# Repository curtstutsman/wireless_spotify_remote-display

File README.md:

Wireless Spotify Remote Control and Display
Curt Stutsman & Nicholas Watanabe
https://github.com/curtstutsman/wireless_spotify_remote-display

Introduction
	Our group elected to implement a wireless Spotify remote control and album art display utilizing Spotify’s API to control the listening state of the user. Some features of the project include a rotary encoder (which doubled as a push button) and a 64x64 LED matrix. The rotary encoder was purposed for all input, allowing the user to adjust volume with rotations and toggle play/pause and skip to next or previous songs with single, double, and triple taps. The LED matrix was the primary output of the system, displaying in real time the album art of whatever song was currently playing. To achieve wireless communication with Spotify’s api, our group employed and ESP32-WROOM-32E wireless module. The rest of the functionality (LED driving, GPIO interface, etc.) was implemented on an STM32F103.

Figure 1: System Block Diagram

Hardware Overview
	Our project did not require an extensive list of hardware components to achieve the desired functionality. For the LED matrix, we used a 64x64 panel purchased from adafruit with a 2.5mm pitch. Each LED held a one bit value for each of red, green, and blue channels. The matrix as a whole was controlled via the HUB75 protocol, a standard for these types of LED matrices that utilized 16 different signals in the case of our matrix. The 16 signals of the HUB75 protocol were connected and controlled from the GPIO pins of the STM32. The rotary encoder was also controlled via GPIO pins on the MCU. We used a simple UART connection between the STM32 and the ESP32 to send commands to the ESP and to receive image data into the STM. A few other trivial components were included in the final PCB design such as reset buttons, headers for programming, and decoupling capacitors. The full schematic and PCB layout is given below and is linked on our github repository.

Figure 2: Schematic

Figure 3: PCB Layout

Software Overview
	Because we utilized two different chips in our project, the software was split between the STM32F103, which handled LED driving and input control, and the ESP32, which handled communication with the Spotify API and JPEG Decoding. All code can be found in the main.c file of the STM32 source code and the esp32_sketch.ino file of the ESP32 source code, both available on the github repo.

	The first functionality implemented was the button control. The rotary encoder consists of three signals, two for rotation encoding and one for the button. All three channels were connected to GPIO pins and configured to interrupt the CPU at the rising edge of the signal. Pushes to the button increase the tap count variable. The main loop would then check if tap count was greater than zero and enough time had passed since the last tap (to account for double and triple taps) and then send the corresponding command over UART to the ESP32. Interrupts for rotation of the encoder worked in a similar fashion, except a comparison had to be done between the two rotation signals to determine if the rotation was clockwise or counter clockwise so we could tell whether to send the increase or decrease volume command. The LED driving code is by far the most complicated of all the software we wrote. The first task was understanding and implementing the HUB75 protocol, which involved the control of 6 different color signals, 5 addressing signals, and 3 control signals all operating in unison to even turn on the display. Another challenge stemmed from the fact that each LED actually only held one bit for red, green, and blue each, meaning if we wanted to display a color that wasn’t a direct combination of these three, we had to implement a PWM control over the LEDs. For example, to display a red color with 50% intensity, we would have to turn on the red color for that pixel for 50% of the cycles. We were able to adequately control this by looping through the range of the bit magnitude of our colors and adjusting the delay the pixel was on for by this magnitude, giving the appearance of different colors. This however, required extremely fast speeds in order to avoid flickering in the display. The actual pixel data was received directly from ESP32 into an image buffer, which was used to draw from.

	In comparison the code for the ESP32 was simpler apart from a few small details. All of the ESP32 development was done in the Arduino IDE, which made programming the chip much easier. Many of the functions were simple HTTP requests based on their respective commands from the rotary encoder input. The ESP32 was constantly listening for these commands over the serial line it shared with the STM32. The ESP was also constantly checking if the album link had changed, meaning a new song was playing and new image data needed to be sent to the STM32. If there was a new song, it was downloaded from the link (which is provided by the Spotify API), saved to SPIFFS (the ESP32’s built in filesystem), decoded into the raw pixel values, formatted to fit our 8 bits of color standard (RGB332) and sent over UART to the STM32 for storage in its image buffer. There are a few authorization requirements as well as set up steps in the Spotify Developer Dashboard to grant permissions to our project to view and control a selected spotify account, but these are not included in our source code and can be deduced from Spotify’s Web API Documentation. 

Design Challenges and Solutions:
An initial challenge we ran into was the wifi module. To begin we first used the ESP8266 which had less capabilities (and was much harder to use than the ESP32). We were originally trying to rely on the AT command set from Espressif to control the chip, however both the ESP8266 and the AT Firmware were unable to connect to the WPA2-Enterprise level security deployed by the IllinoisNet wifi network. Also, employing only AT commands would not give us enough control over the wireless chip. As a solution, we switched to the more powerful ESP32 and the Arduino IDE, which allowed us to upload code straight to the chip as well as utilize some helpful WiFi libraries.

Another large issue we faced was the refresh rate of the LED matrix. Matrices controlled by the HUB75 protocol only actually turn on two rows of LEDs at a time, and only while the Output Enable signal is high. The rows are cycled on and on so fast that to the human eye it appears to be a fully lit screen. However, if the driver is not updating the rows fast enough, major flickering will occur on the screen. Furthermore, implementing PWM and more than 3 bits of color meant even more cycles until an entire image was properly displayed (and more memory to store the image buffer). To overcome this, we elected to use a larger and faster MCU than the standard STM32L0 given to us. We also spent a lot of time optimizing our main display loop, trying to avoid calculations within the loop wherever possible and instead relying on lookup-tables defined on startup for proper calculations. We also had to bypass the HAL interface for writing to the GPIO pins, and instead wrote directly to the GPIO registers on the chip. 

 When we implemented the PCB board we ran into the issue uploading code. The new STM we used for the PCB (STM32F103) needs to have the reset pin connected to the programmer when uploading code. To solve this we soldered a wire to both pins on the PCB. Furthermore, we had to create two different voltage sources as our rotary encoder required 5V to operate while the rest of the components like the microcontroller and wifi module required 3.3V.

Project Replication

If one wishes to replicate this project in its entirety, the steps taken are as follows:

1. Download the gbr files from github repo, and send them to your favorite pcb manufacturer (you may want to make the wiring changes mentioned in the third paragraph of section IV).
2. Purchase the parts listed in FinalPCBBoard1/FinalPCBBoard1.xml in the repo
3. Solder all of the components to the board
4. Program the ESP32 using the Arduino IDE and the provided sketch + libraries
5. Create a new STM32 project selecting the F103 as the part and add all of the files from the github repo (be sure the pinouts are the same as the final.ioc file)
6. Program the STM32 and ESP32 on your PCB
7. Supply 3.3V directly to the LDO output pins
8. Apply a 5V souce to the power source on the rotary encoder

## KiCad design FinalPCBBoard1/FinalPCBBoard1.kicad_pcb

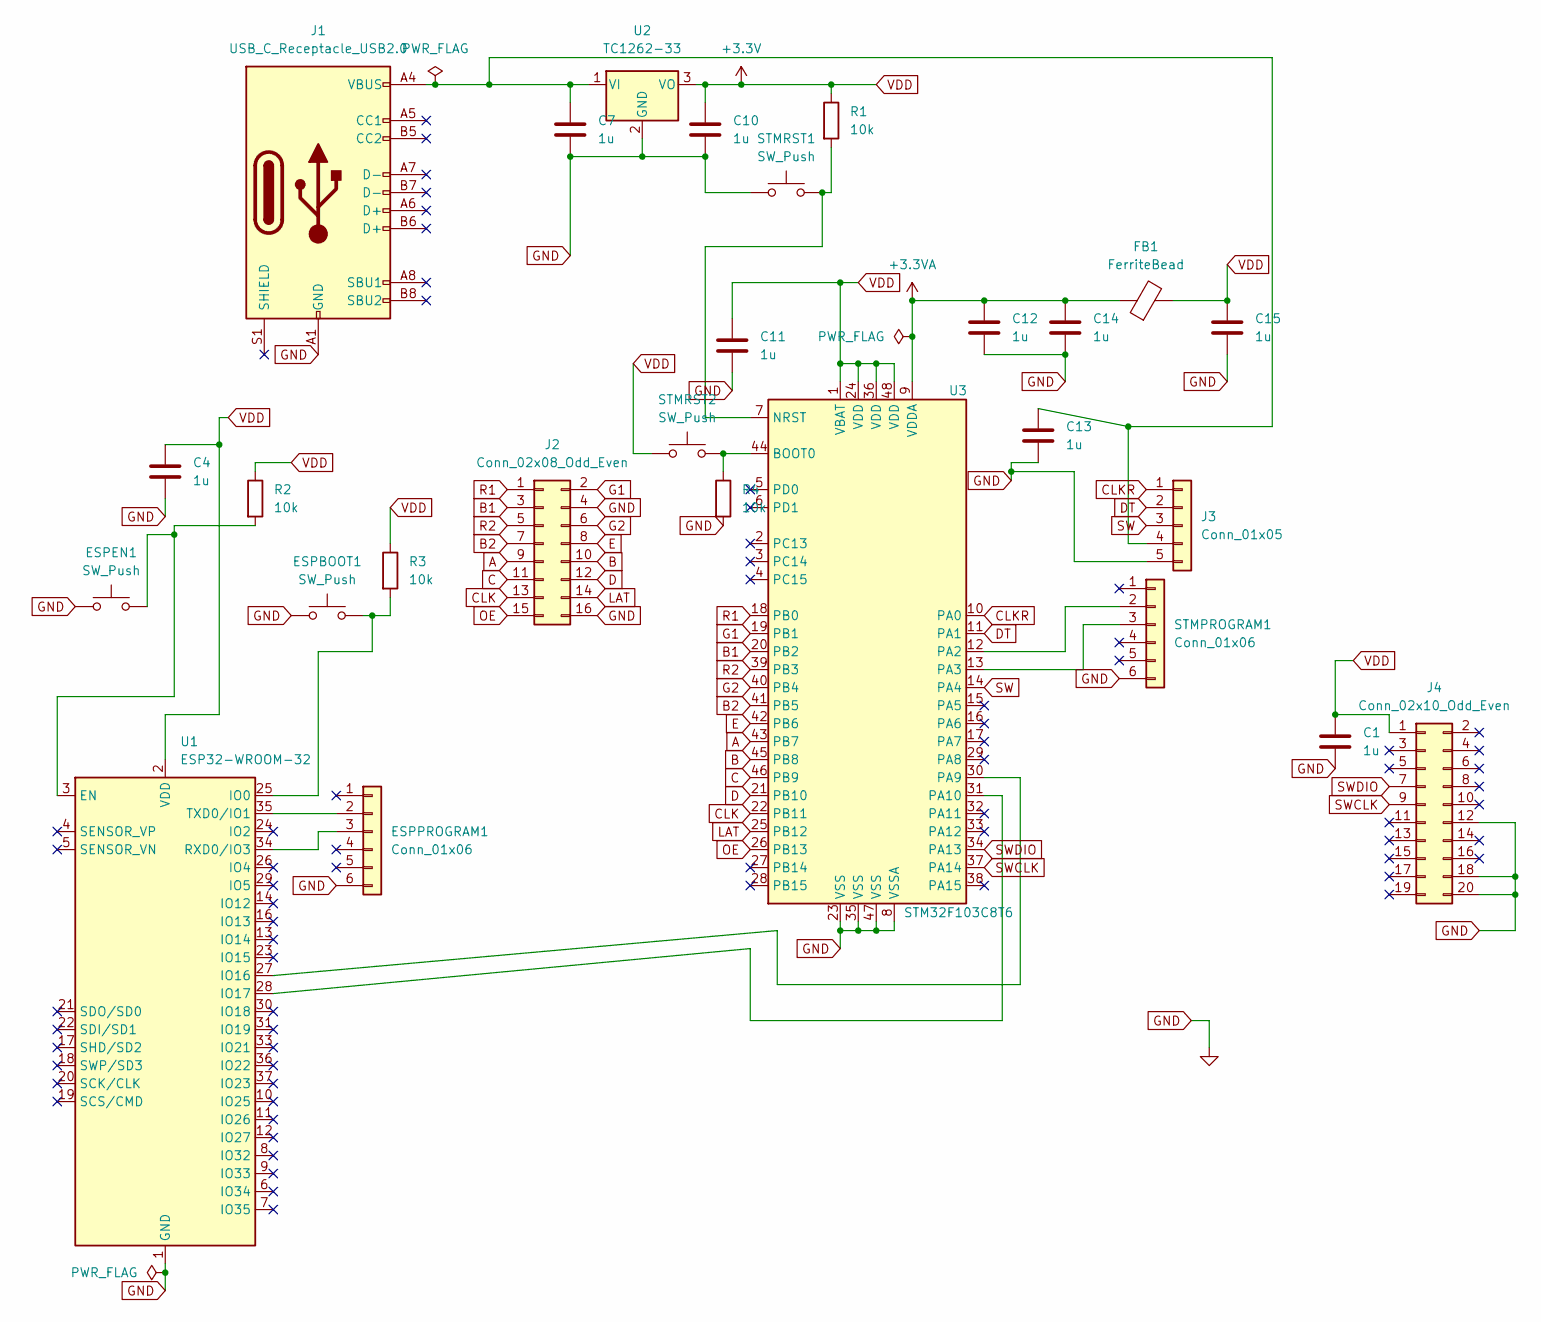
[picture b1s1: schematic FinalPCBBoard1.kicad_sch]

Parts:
C1, C4, C7, C10, C11, C12, C13, C14, C15: 1u; C_0805_2012Metric_Pad1.18x1.45mm_HandSolder
ESPBOOT1: SW_Push; SW_PUSH_6mm_H4.3mm
ESPEN1: SW_Push; SW_PUSH_6mm_H4.3mm
ESPPROGRAM1: Conn_01x06; PinSocket_1x06_P2.54mm_Horizontal
FB1: FerriteBead; LairdTech_28C0236-0JW-10
J1: USB_C_Receptacle_USB2.0; USB_C_Receptacle_GCT_USB4085
J2: Conn_02x08_Odd_Even; PinHeader_2x08_P2.54mm_Vertical
J3: Conn_01x05; PinSocket_1x05_P2.54mm_Horizontal
J4: Conn_02x10_Odd_Even; PinSocket_2x10_P2.54mm_Vertical
R1, R2, R3, R4: 10k; R_0805_2012Metric_Pad1.20x1.40mm_HandSolder
STMPROGRAM1: Conn_01x06; PinSocket_1x06_P2.54mm_Vertical
STMRST1, STMRST2: SW_Push; SW_PUSH_6mm_H4.3mm
U1: ESP32-WROOM-32
U2: TC1262-33; SOT-223
U3: STM32F103C8T6; LQFP-48_7x7mm_P0.5mm

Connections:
+3.3VA: C12.1, C14.1, FB1.1, U3.9 (VDDA)
A: J2.9, U3.43 (PB7)
B: J2.10, U3.45 (PB8)
B1: J2.3, U3.20 (PB2)
B2: J2.7, U3.41 (PB5)
C: J2.11, U3.46 (PB9)
CLK: J2.13, U3.22 (PB11)
CLKR: J3.1, U3.10 (PA0)
D: J2.12, U3.21 (PB10)
DT: J3.2, U3.11 (PA1)
E: J2.8, U3.42 (PB6)
G1: J2.2, U3.19 (PB1)
G2: J2.6, U3.40 (PB4)
GND: C1.2, C4.2, C7.2, C10.2, C11.2, C12.2, C13.2, C14.2, C15.2, ESPBOOT1.1, ESPEN1.1, ESPPROGRAM1.6, J1.A1 (GND), J1.A12 (GND), J1.B1 (GND), J1.B12 (GND), J2.4, J2.16, J3.5, J4.12, J4.18, J4.20, R4.2, STMPROGRAM1.6, STMRST1.1, U1.1 (GND), U1.15 (GND), U1.38 (GND), U1.39 (GND), U2.2 (GND), U3.8 (VSSA), U3.23 (VSS), U3.35 (VSS), U3.47 (VSS)
LAT: J2.14, U3.25 (PB12)
unnamed: C7.1, C13.1, J1.A4 (VBUS), J1.A9 (VBUS), J1.B4 (VBUS), J1.B9 (VBUS), J3.4, U2.1 (VI)
unnamed: ESPBOOT1.2, R3.2, U1.25 (IO0)
unnamed: ESPEN1.2, R2.2, U1.3 (EN)
unnamed: ESPPROGRAM1.2, U1.35 (TXD0/IO1)
unnamed: ESPPROGRAM1.3, U1.34 (RXD0/IO3)
unnamed: R1.2, STMRST1.2, U3.7 (NRST)
unnamed: STMPROGRAM1.2, U3.12 (PA2)
unnamed: STMPROGRAM1.3, U3.13 (PA3)
unnamed: U1.27 (IO16), U3.30 (PA9)
unnamed: U1.28 (IO17), U3.31 (PA10)
unnamed: R4.1, STMRST2.2, U3.44 (BOOT0)
OE: J2.15, U3.26 (PB13)
R1: J2.1, U3.18 (PB0)
R2: J2.5, U3.39 (PB3)
SW: J3.3, U3.14 (PA4)
SWCLK: J4.9, U3.37 (PA14)
SWDIO: J4.7, U3.34 (PA13)
VDD: C1.1, C4.1, C10.1, C11.1, C15.1, FB1.2, J4.1, R1.1, R2.1, R3.1, STMRST2.1, U1.2 (VDD), U2.3 (VO), U3.1 (VBAT), U3.24 (VDD), U3.36 (VDD), U3.48 (VDD)

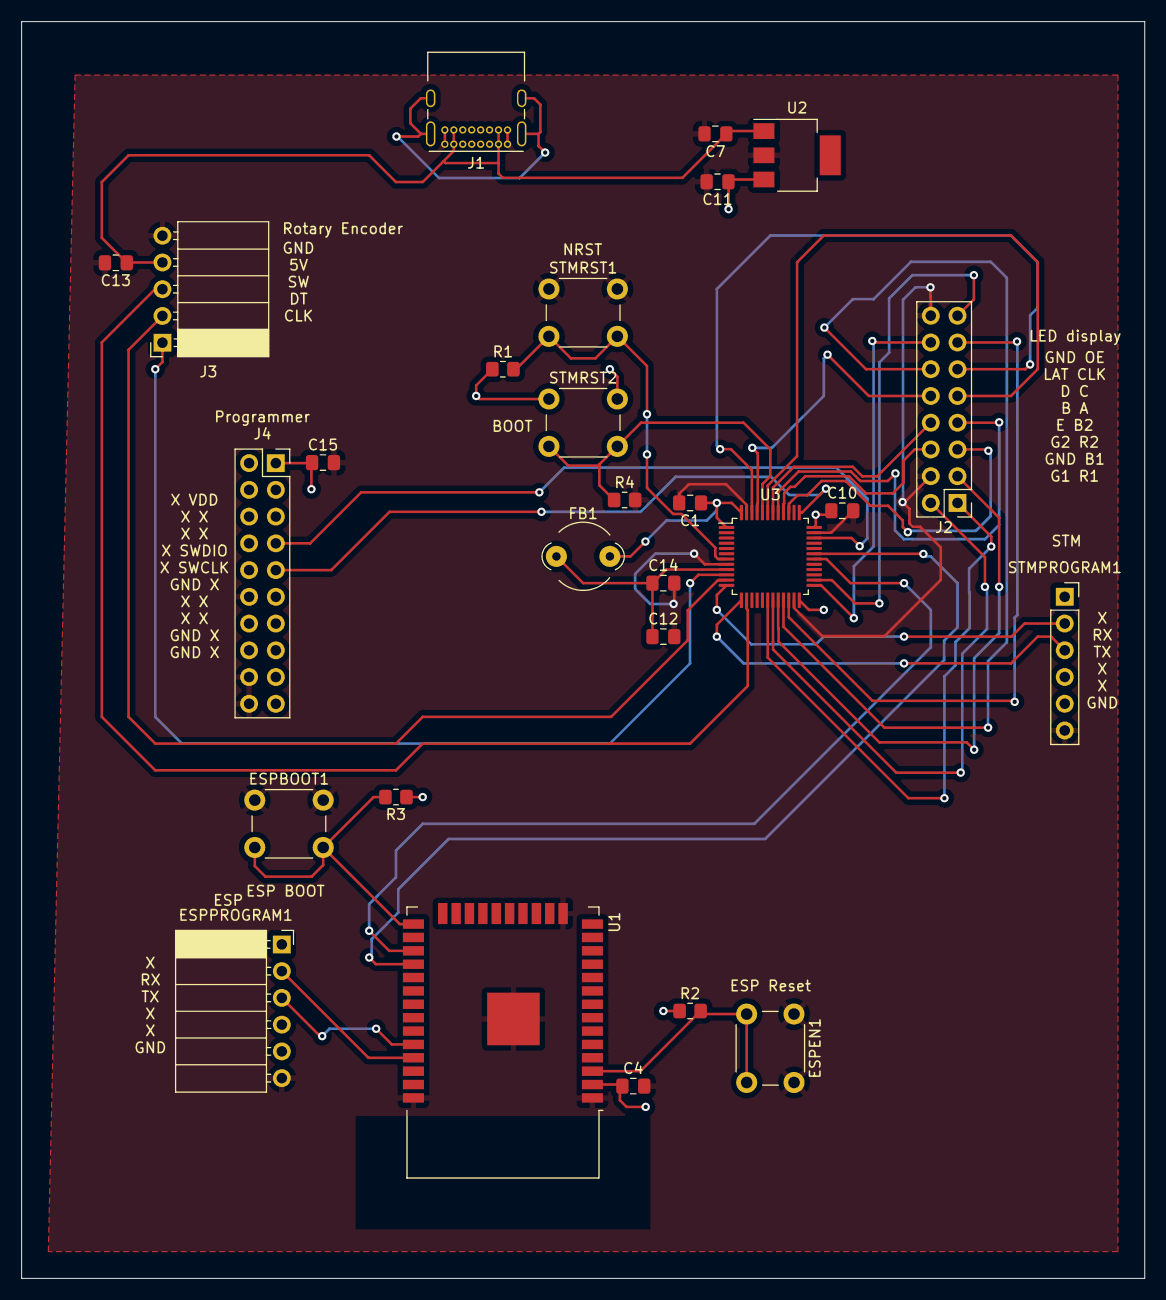
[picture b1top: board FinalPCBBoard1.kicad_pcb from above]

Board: 2 copper layers, 106.7 x 119.4 mm, 27 parts (0 on the bottom side), 33 nets.

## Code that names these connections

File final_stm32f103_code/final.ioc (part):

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Mcu.Name=STM32F103C(8-B)Tx
Mcu.Package=LQFP48
Mcu.UserName=STM32F103C8Tx
PA0-WKUP.Signal=GPXTI0
PA1.Signal=GPXTI1
PA10.Mode=Asynchronous
PA10.Signal=USART1_RX
PA13.Signal=SYS_JTMS-SWDIO
PA14.Signal=SYS_JTCK-SWCLK
PA2.Mode=Asynchronous
PA2.Signal=USART2_TX
PA3.Mode=Asynchronous
PA3.Signal=USART2_RX
PA4.GPIOParameters=GPIO_ModeDefaultEXTI
PA4.GPIO_ModeDefaultEXTI=GPIO_MODE_IT_RISING
PA4.Signal=GPXTI4
PA9.Mode=Asynchronous
PA9.Signal=USART1_TX
PB0.GPIOParameters=GPIO_Speed
PB0.GPIO_Speed=GPIO_SPEED_FREQ_HIGH
PB0.Signal=GPIO_Output
PB1.GPIOParameters=GPIO_Speed
PB1.GPIO_Speed=GPIO_SPEED_FREQ_HIGH
PB1.Signal=GPIO_Output
PB10.GPIOParameters=GPIO_Speed
PB10.GPIO_Speed=GPIO_SPEED_FREQ_HIGH
PB10.Signal=GPIO_Output
PB11.GPIOParameters=GPIO_Speed
PB11.GPIO_Speed=GPIO_SPEED_FREQ_HIGH
PB11.Signal=GPIO_Output
PB12.GPIOParameters=GPIO_Speed
PB12.GPIO_Speed=GPIO_SPEED_FREQ_HIGH
PB12.Signal=GPIO_Output
PB13.GPIOParameters=GPIO_Speed
PB13.GPIO_Speed=GPIO_SPEED_FREQ_HIGH
PB13.Signal=GPIO_Output
PB2.GPIOParameters=GPIO_Speed
PB2.GPIO_Speed=GPIO_SPEED_FREQ_HIGH
PB2.Signal=GPIO_Output
PB3.GPIOParameters=GPIO_Speed
PB3.GPIO_Speed=GPIO_SPEED_FREQ_HIGH
PB3.Signal=GPIO_Output
PB4.GPIOParameters=GPIO_Speed
PB4.GPIO_Speed=GPIO_SPEED_FREQ_HIGH
PB4.Signal=GPIO_Output
PB5.GPIOParameters=GPIO_Speed
PB5.GPIO_Speed=GPIO_SPEED_FREQ_HIGH
PB5.Signal=GPIO_Output
PB6.GPIOParameters=GPIO_Speed
PB6.GPIO_Speed=GPIO_SPEED_FREQ_HIGH
PB6.Signal=GPIO_Output
PB7.GPIOParameters=GPIO_Speed
PB7.GPIO_Speed=GPIO_SPEED_FREQ_HIGH
PB7.Signal=GPIO_Output
PB8.GPIOParameters=GPIO_Speed
PB8.GPIO_Speed=GPIO_SPEED_FREQ_HIGH
PB8.Signal=GPIO_Output
PB9.GPIOParameters=GPIO_Speed
PB9.GPIO_Speed=GPIO_SPEED_FREQ_HIGH
PB9.Signal=GPIO_Output
RCC.SYSCLKFreq_VALUE=64000000
RCC.SYSCLKSource=RCC_SYSCLKSOURCE_PLLCLK
board=custom

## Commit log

2024-12-17 Removing Secrets
2024-12-17 ReadMe
